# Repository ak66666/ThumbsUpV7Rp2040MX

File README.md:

# ThumbsUp! v7 RP2040-based keyboard for MX switches

Multilevel 56/58 Key Split Contoured Keyboard.
2- or 3-key Thumb Cluster

* RP2040 is soldered on the boards.
* TRS (3-wire) audio cable to connect the halves.
* Hot swap sockets for MX switches.
* USB-C connectors.
* Connects to computer from either side, halves could be used separately.
* 3 different layouts for the 3-key cluster.

Board needs 3D printed switch plates: https://github.com/ak66666/ThubmsUpSwitchPlates

Other pictures in Photos folder.

# Firmware

Please refer to this article:
https://thumbsupkeyboards.blogspot.com/2024/02/source-files-and-default-firmware.html

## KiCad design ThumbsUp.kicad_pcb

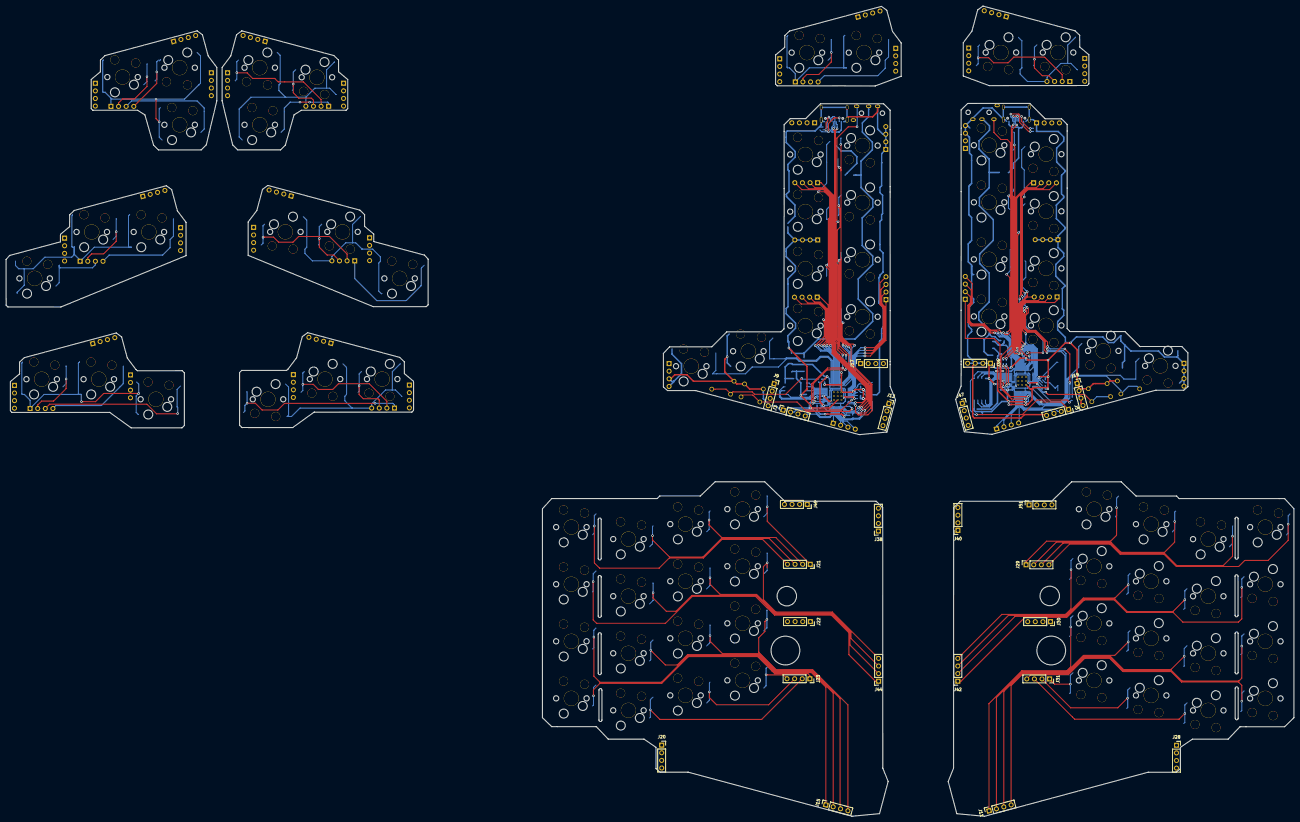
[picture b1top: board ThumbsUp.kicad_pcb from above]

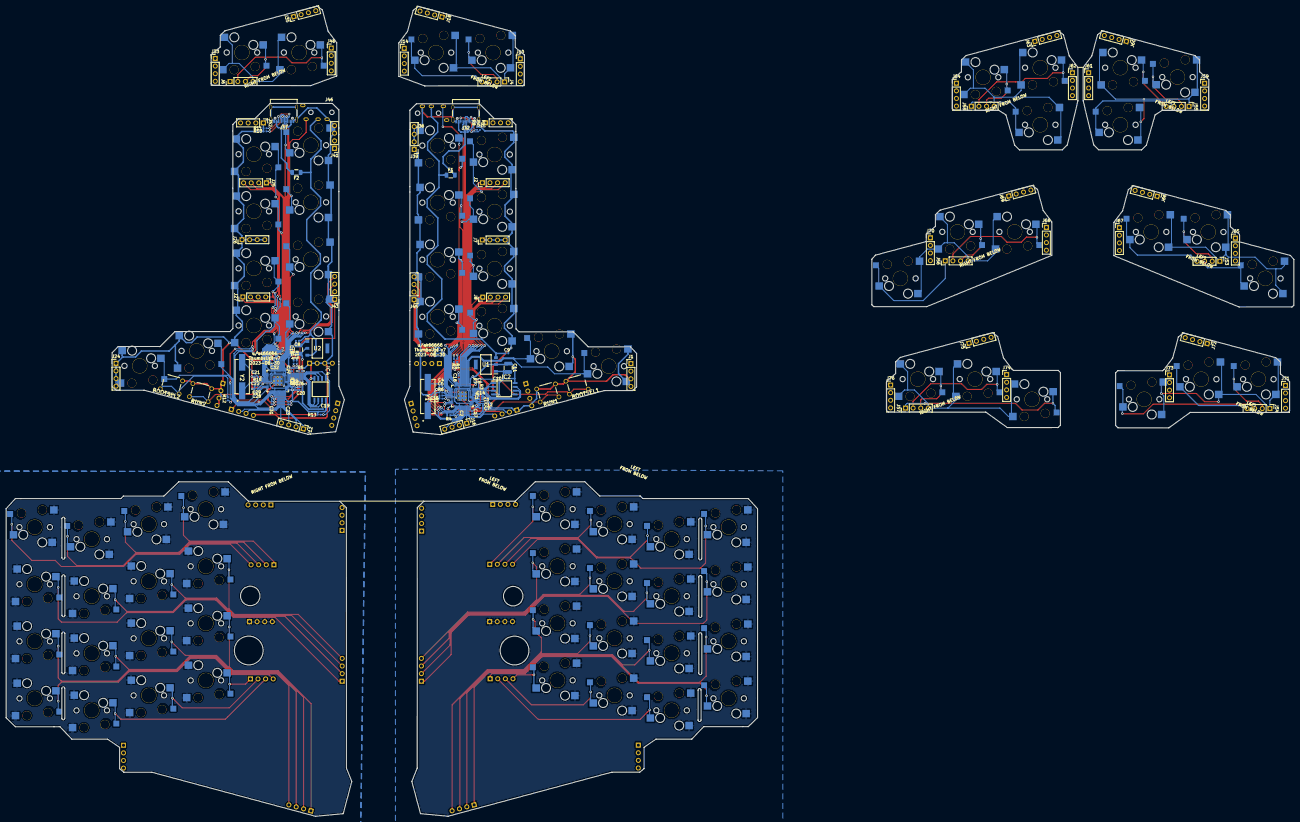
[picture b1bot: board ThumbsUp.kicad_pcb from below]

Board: 2 copper layers, 429.9 x 270.5 mm, 210 parts (112 on the bottom side), 163 nets.

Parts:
BOOTSEL1, BOOTSEL2: BUTT-4; BUTT4
C2, C6, C7, C10, C13, C14, C15, C16, C17, C19, C23, C25, C26, C27, C28, C29, C31, C32: 0.1uF; C_0402_1005Metric
C3, C12, C20, C24: 1uF; C_0402_1005Metric
C4, C5, C21, C22: 27pF; C_0402_1005Metric
C8, C9: 10uF; C_0402_1005Metric
C11, C18: 100uF; C_1210_3225Metric
F1, F2: Polyfuse; Fuse_1206_3216Metric
IC1, IC3: RP2040; RP2040-QFN-56
IC2, IC4: W25Q128JVSIM; SOIC127P790X216-8N
J1, J2, J4, J6, J7, J8, J24, J25, J26, J27, J53, J54, J55, J56, J57, J58: Conn_01x04_Male; PinHeader_1x04_P2.54mm_Vertical
J3, J5, J20, J21, J22, J23, J28, J29, J30, J31: Conn_01x04_Female; PinSocket_1x04_P2.54mm_Vertical
J9, J11, J13, J15, J17, J19, J34, J38, J40, J42, J44, J47, J49, J51: Raiser_Female; PinSocket_1x04_P2.54mm_Vertical
J10, J12, J14, J16, J18, J33, J35, J39, J41, J43, J45, J48, J50, J52, J59, J60, J61, J62, J63, J64, J65, J66, J67, J68, J69, J70, J71, J72, J73, J74, J75, J76: Raiser_Male; PinHeader_1x04_P2.54mm_Vertical
J32, J37: USB_C_Receptacle_USB2.0; USB_C_Receptacle_Palconn_UTC16-G
J36, J46: PJ-3200B; PJ-3200B-4A
MX1: SwESC; MX-GLP2-HotSwap
MX2: SwTAB; MX-GLP2-HotSwap
MX3: SwLCTL; MX-GLP2-HotSwap
MX4: SwQ; MX-GLP2-HotSwap
MX5: SwA; MX-GLP2-HotSwap
MX6: SwZ; MX-GLP2-HotSwap
MX7: SwW; MX-GLP2-HotSwap
MX8: SwS; MX-GLP2-HotSwap
MX9: SwX; MX-GLP2-HotSwap
MX10: SwLWIN; MX-GLP2-HotSwap
MX11: SwE; MX-GLP2-HotSwap
MX12: SwD; MX-GLP2-HotSwap
MX13: SwC; MX-GLP2-HotSwap
MX14: SwLALT; MX-GLP2-HotSwap
MX15: SwR; MX-GLP2-HotSwap
MX16: SwF; MX-GLP2-HotSwap
MX17: SwV; MX-GLP2-HotSwap
MX18, MX62, MX63, MX64: SwLMOD; MX-GLP2-HotSwap
MX19: SwT; MX-GLP2-HotSwap
MX20: SwG; MX-GLP2-HotSwap
MX21: SwB; MX-GLP2-HotSwap
MX22, MX59, MX60, MX61: SwLSHFT; MX-GLP2-HotSwap
MX23: SwY; MX-GLP2-HotSwap
MX24: SwH; MX-GLP2-HotSwap
MX25: SwN; MX-GLP2-HotSwap
MX26, MX74, MX75, MX76: SwRSHFT; MX-GLP2-HotSwap
MX27: SwU; MX-GLP2-HotSwap
MX28: SwJ; MX-GLP2-HotSwap
MX29: SwM; MX-GLP2-HotSwap
MX30, MX71, MX72, MX73: SwRMOD; MX-GLP2-HotSwap
MX31: SwI; MX-GLP2-HotSwap
MX32: SwK; MX-GLP2-HotSwap
MX33: SwCOMMA; MX-GLP2-HotSwap
MX34: SwRALT; MX-GLP2-HotSwap
MX35: SwO; MX-GLP2-HotSwap
MX36: SwL; MX-GLP2-HotSwap
MX37: SwDOT; MX-GLP2-HotSwap
MX38: SwMENU; MX-GLP2-HotSwap
MX39: SwP; MX-GLP2-HotSwap
MX40: SwCOLON; MX-GLP2-HotSwap
MX41: Sw?; MX-GLP2-HotSwap
MX42: SwBKSP; MX-GLP2-HotSwap
MX43: SwENTER; MX-GLP2-HotSwap
MX44: SwRCTRL; MX-GLP2-HotSwap
MX45: SwGrave; MX-GLP2-HotSwap
MX46: Sw1; MX-GLP2-HotSwap
MX47: Sw2; MX-GLP2-HotSwap
MX48: Sw3; MX-GLP2-HotSwap
MX49: Sw4; MX-GLP2-HotSwap
MX50: Sw5; MX-GLP2-HotSwap
MX51: Sw6; MX-GLP2-HotSwap
MX52: Sw7; MX-GLP2-HotSwap
MX53: Sw8; MX-GLP2-HotSwap
MX54: Sw9; MX-GLP2-HotSwap
MX55: Sw0; MX-GLP2-HotSwap
MX56: SwDEL; MX-GLP2-HotSwap
MX65, MX66, MX67: SwThL; MX-GLP2-HotSwap
MX68, MX69, MX70: SwThR; MX-GLP2-HotSwap
R1, R2, R14, R15: 27.4; R_0402_1005Metric
R3, R12: 10k; R_0402_1005Metric
R4, R5: 5.1K; R_0402_1005Metric
R6, R16: 1k; R_0402_1005Metric
R7, R13: 10K; R_0402_1005Metric
R8, R9, R10, R11: 5.1k; R_0402_1005Metric
RUN1, RUN2: BUTT-4; BUTT4
U1, U2: AMS1117-3.3_SOT223; SOT229P700X180-4N
Y1, Y2: ABLS-12.000MHZ-B4-T; HC%2f49US-(AT49)_1

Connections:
+1V1: C12.1, C13.1, C14.1, C24.1, C26.1, C28.1, IC1.23, IC1.45, IC1.50, IC3.23, IC3.45, IC3.50
+3V3: C2.1, C3.1, C6.1, C7.1, C10.1, C11.1, C15.1, C16.1, C17.1, C18.1, C19.1, C20.1, C23.1, C25.1, C27.1, C29.1, C31.1, C32.1, IC1.1, IC1.10, IC1.22, IC1.33, IC1.42, IC1.43, IC1.44, IC1.48, IC1.49, IC2.8, IC3.1, IC3.10, IC3.22, IC3.33, IC3.42, IC3.43, IC3.44, IC3.48, IC3.49, IC4.8, R4.1, R5.2, R7.2, R13.2, U1.2, U2.2
+5VA: F1.2, F2.2, J32.A4, J32.A9, J32.B4, J32.B9, J37.A4, J37.A9, J37.B4, J37.B9
D+: J32.A6, J32.B6, R2.2
D-: J32.A7, J32.B7, R1.2
K_0: IC3.14, J25.2
K_1: IC1.31, J2.3
K_2: IC1.34, J2.2
K_3: IC1.35, J2.1
K_4: IC1.27, MX49.2
K_5: IC1.28, MX50.2
K_6: IC3.12, MX51.2
K_7: IC3.35, MX52.2
K_8: IC3.28, J25.4
K_9: IC3.27, J25.3
K_A: IC1.38, J16.2
K_B: IC1.14, MX21.2
K_BSPC: IC3.34, J43.1
K_C: IC1.5, J8.4
K_COMM: IC3.18, J27.1
K_D: IC1.36, J16.4
K_DEL: IC3.13, J25.1
K_DOT: IC3.17, J27.2
K_E: IC1.15, J45.4
K_ENT: IC3.38, J12.4
K_ESC: IC1.18, J45.1
K_F: IC1.9, MX16.2
K_G: IC1.13, MX20.2
K_GRAVE: IC1.30, J2.4
K_H: IC3.6, MX24.2
K_I: IC3.4, J43.4
K_J: IC3.11, MX28.2
K_K: IC3.41, J12.1
K_L: IC3.40, J12.2
K_LALT: IC1.3, MX14.2
K_LCTL: IC1.8, J8.1
K_LSFT: IC1.41, J3.2
K_LWR: IC3.36, J5.2
K_M: IC3.9, MX29.2
K_MNU: IC3.31, MX38.2
K_N: IC3.7, MX25.2
K_O: IC3.3, J43.3
K_P: IC3.2, J43.2
K_Q: IC1.17, J45.2
K_R: IC1.11, MX15.2
K_RALT: IC3.30, MX34.2
K_RCTL: IC3.15, J27.4
K_RSE: IC1.40, J3.4
K_RSFT: IC3.37, J5.3
K_S: IC1.37, J16.3
K_SEMICOL: IC3.39, J12.3
K_SLASH: IC3.16, J27.3
K_T: IC1.12, MX19.2
K_TAB: IC1.39, J16.1
K_THL: IC1.29, J3.3
K_THR: IC3.29, J5.1
K_U: IC3.8, MX27.2
K_V: IC1.4, MX17.2
K_W: IC1.16, J45.3
K_WIN: IC1.2, MX10.2
K_X: IC1.6, J8.3
K_Y: IC3.5, MX23.2
K_Z: IC1.7, J8.2
L-BASE: BOOTSEL1.D1, BOOTSEL2.B1, C2.2, C3.2, C4.2, C5.2, C6.2, C7.2, C8.2, C9.2, C10.2, C11.2, C12.2, C13.2, C14.2, C15.2, C16.2, C17.2, C18.2, C19.2, C20.2, C21.2, C22.2, C23.2, C24.2, C25.2, C26.2, C27.2, C28.2, C29.2, C31.2, C32.2, IC1.19, IC1.57, IC2.4, IC3.19, IC3.57, IC4.4, J1.3, J1.4, J3.1, J5.4, J7.1, J7.2, J7.3, J7.4, J9.4, J19.1, J19.2, J19.3, J19.4, J24.1, J24.2, J24.3, J24.4, J26.1, J26.2, J26.3, J26.4, J32.A1, J32.A12, J32.B1, J32.B12, J32.S1, J34.1, J34.2, J34.3, J34.4, J36.1, J37.A1, J37.A12, J37.B1, J37.B12, J37.S1, J39.1, J39.2, J39.3, J39.4, J41.3, J41.4, J46.1, J52.1, MX10.1, MX14.1, MX15.1, MX16.1, MX17.1, MX19.1, MX20.1, MX21.1, MX23.1, MX24.1, MX25.1, MX27.1, MX28.1, MX29.1, MX34.1, MX38.1, MX49.1, MX50.1, MX51.1, MX52.1, R8.2, R9.1, R10.2, R11.1, RUN1.B1, RUN1.D1, RUN2.B1, RUN2.D1, U1.1, U2.1
L-RING1: C8.1, C9.1, F1.1, F2.1, J36.2, J46.2, U1.3, U2.3
L-TIP: IC1.32, J36.3, R4.2
unnamed: BOOTSEL1.A1, BOOTSEL1.C1, R3.1
unnamed: BOOTSEL2.A1, BOOTSEL2.C1, R12.1
unnamed: C5.1, R6.2, Y1.1
unnamed: C22.1, R16.2, Y2.1
unnamed: IC1.26, RUN1.A1, RUN1.C1
unnamed: IC1.46, R1.1
unnamed: IC1.47, R2.1
unnamed: IC3.26, RUN2.A1, RUN2.C1
unnamed: IC3.46, R15.1
unnamed: IC3.47, R14.1
unnamed: J4.1, MX18.1, MX22.1
unnamed: J4.2, MX22.2
unnamed: J4.4, MX18.2
unnamed: J6.2, MX30.2
unnamed: J6.3, MX26.2
unnamed: J6.4, MX26.1, MX30.1
unnamed: J11.1, MX32.2
unnamed: J11.2, MX36.2
unnamed: J11.3, MX40.2
unnamed: J11.4, MX43.2
unnamed: J15.1, MX2.2
unnamed: J15.2, MX5.2
unnamed: J15.3, MX8.2
unnamed: J15.4, MX12.2
unnamed: J21.1, MX48.2
unnamed: J21.2, MX47.2
unnamed: J21.3, MX46.2
unnamed: J21.4, MX45.2
unnamed: J22.1, J22.2, J22.3, J22.4, MX1.1, MX2.1, MX3.1, MX4.1, MX5.1, MX6.1, MX7.1, MX8.1, MX9.1, MX11.1, MX12.1, MX13.1, MX45.1, MX46.1, MX47.1, MX48.1
unnamed: J23.1, MX3.2
unnamed: J23.2, MX6.2
unnamed: J23.3, MX9.2
unnamed: J23.4, MX13.2
unnamed: J29.1, MX53.2
unnamed: J29.2, MX54.2
unnamed: J29.3, MX55.2
unnamed: J29.4, MX56.2
unnamed: J30.1, J30.2, J30.3, J30.4, MX31.1, MX32.1, MX33.1, MX35.1, MX36.1, MX37.1, MX39.1, MX40.1, MX41.1, MX42.1, MX43.1, MX44.1, MX53.1, MX54.1, MX55.1, MX56.1
unnamed: J31.1, MX33.2
unnamed: J31.2, MX37.2
unnamed: J31.3, MX41.2
unnamed: J31.4, MX44.2
unnamed: J32.A5, R8.1
unnamed: J32.B5, R9.2
unnamed: J37.A5, R10.1
unnamed: J37.B5, R11.2
unnamed: J42.1, MX42.2
unnamed: J42.2, MX39.2
unnamed: J42.3, MX35.2
unnamed: J42.4, MX31.2
unnamed: J44.1, MX1.2
unnamed: J44.2, MX4.2
unnamed: J44.3, MX7.2
unnamed: J44.4, MX11.2
unnamed: J53.1, MX59.1, MX62.1, MX65.1
unnamed: J53.2, MX59.2
unnamed: J53.3, MX65.2
unnamed: J53.4, MX62.2
unnamed: J54.1, MX60.1, MX63.1, MX66.1
unnamed: J54.2, MX60.2
unnamed: J54.3, MX66.2
unnamed: J54.4, MX63.2
unnamed: J55.1, MX61.1, MX64.1, MX67.1
unnamed: J55.2, MX61.2
unnamed: J55.3, MX67.2
unnamed: J55.4, MX64.2
unnamed: J56.1, MX68.2
unnamed: J56.2, MX71.2
unnamed: J56.3, MX74.2
unnamed: J56.4, MX68.1, MX71.1, MX74.1
unnamed: J57.1, MX69.2
unnamed: J57.2, MX72.2
unnamed: J57.3, MX75.2
unnamed: J57.4, MX69.1, MX72.1, MX75.1
unnamed: J58.1, MX70.2
unnamed: J58.2, MX73.2
unnamed: J58.3, MX76.2
unnamed: J58.4, MX70.1, MX73.1, MX76.1
QSPI_SCLK: IC1.52, IC2.6
QSPI_SD0: IC1.53, IC2.5
QSPI_SD1: IC1.55, IC2.2
QSPI_SD2: IC1.54, IC2.3
QSPI_SD3: IC1.51, IC2.7
QSPI_SSN: IC1.56, IC2.1, R3.2, R7.1
R-TIP: IC3.32, J46.3, R5.1
RD+: J37.A6, J37.B6, R14.2
RD-: J37.A7, J37.B7, R15.2
RQSPI_SCLK: IC3.52, IC4.6
RQSPI_SD0: IC3.53, IC4.5
RQSPI_SD1: IC3.55, IC4.2
RQSPI_SD2: IC3.54, IC4.3
RQSPI_SD3: IC3.51, IC4.7
RQSPI_SSN: IC3.56, IC4.1, R12.2, R13.1
RXIN: C21.1, IC3.20, Y2.2
RXOUT: IC3.21, R16.1
XIN: C4.1, IC1.20, Y1.2
XOUT: IC1.21, R6.1

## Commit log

2023-08-26 Created v7 from v4
2023-08-27 Wired both RP2040s
2023-08-31 Layed out tracks on L2
2023-09-02 Layed out tracks on R2
2023-09-02 Layed out tracks on the bottom level havles
2023-09-03 Adding the 3key thumbclusters
2023-09-04 Tracedd the 3key thumbclusters
2023-09-09 Put the silkscreens on, ready for Gerbers creation
2023-09-09 Gerber files generated
2023-10-05 Updated BOMs, Gerbers.
2023-10-24 Corrected switch footprint for Gateron sockets
2025-02-27 ThumbsUp v7: Added photos, updated description.
